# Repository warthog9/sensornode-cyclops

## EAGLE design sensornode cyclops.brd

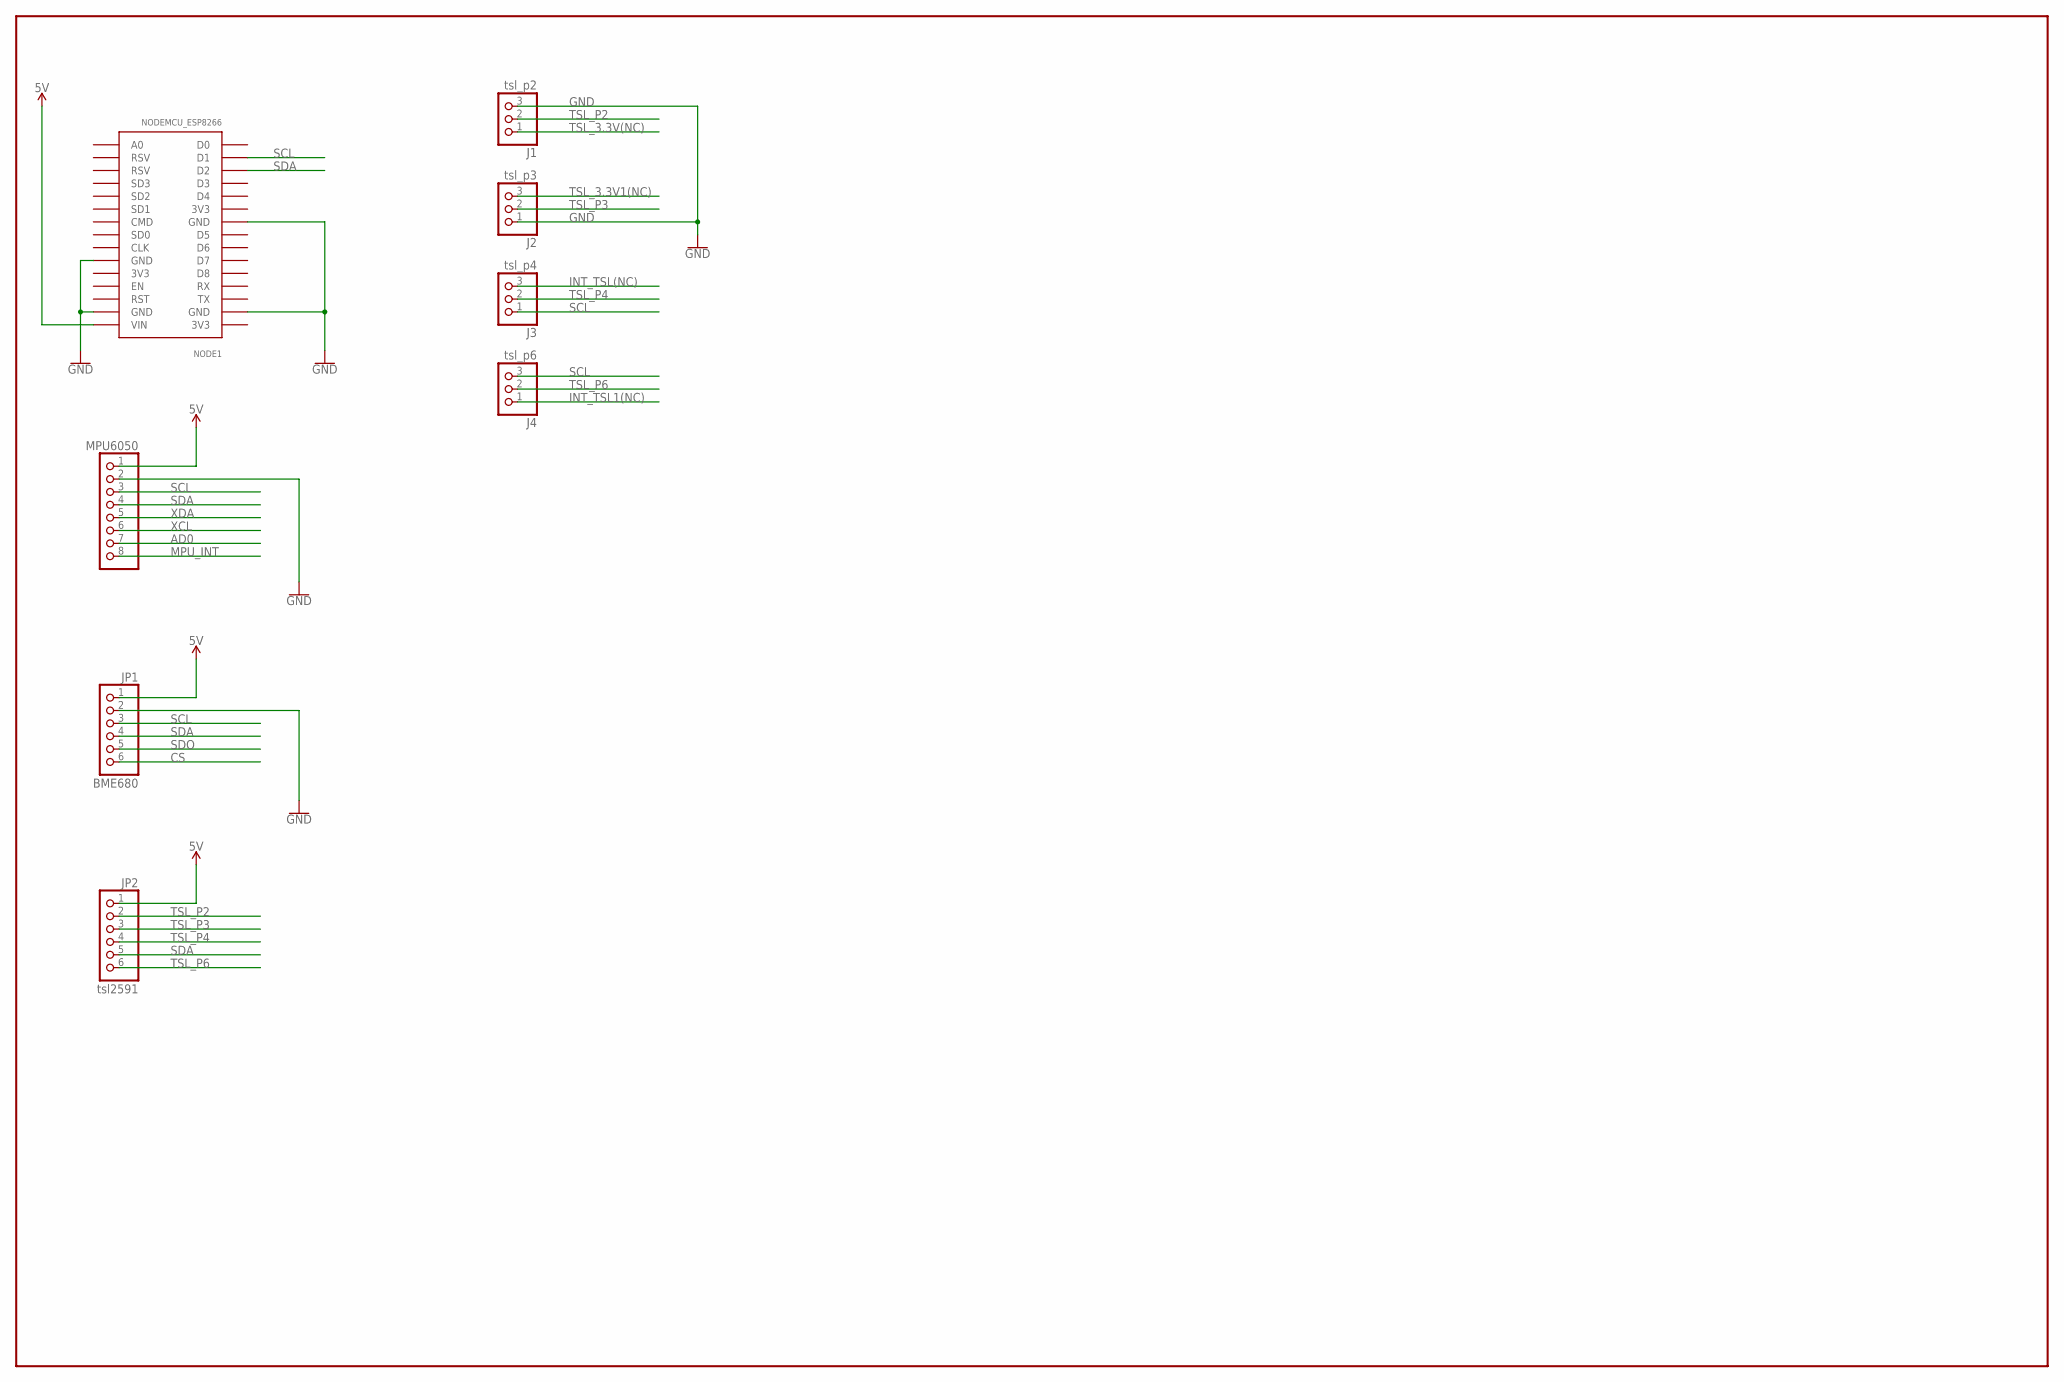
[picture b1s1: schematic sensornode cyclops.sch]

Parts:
J1: tsl_p2; 1X03
J2: tsl_p3; 1X03
J3: tsl_p4; 1X03
J4: tsl_p6; 1X03
JP1: BME680; 1X06
JP2: tsl2591; 1X06
MPU6050: PINHD-1X8; 1X08
NODE1: NODEMCU_ESP8266

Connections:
3V3: NODE1.3V3@1 (3V3), NODE1.3V3@2 (3V3), NODE1.3V3@3 (3V3)
5V: JP1.1, JP2.1, MPU6050.1, NODE1.VIN
AD0: MPU6050.7
CS: JP1.6
GND: J1.3, J2.1, JP1.2, MPU6050.2, NODE1.GND@1 (GND), NODE1.GND@2 (GND), NODE1.GND@3 (GND), NODE1.GND@4 (GND)
INT_TSL1(NC): J4.1
INT_TSL(NC): J3.3
MPU_INT: MPU6050.8
SCL: J3.1, J4.3, JP1.3, MPU6050.3, NODE1.D1
SDA: JP1.4, JP2.5, MPU6050.4, NODE1.D2
SDO: JP1.5
TSL_3.3V1(NC): J2.3
TSL_3.3V(NC): J1.1
TSL_P2: J1.2, JP2.2
TSL_P3: J2.2, JP2.3
TSL_P4: J3.2, JP2.4
TSL_P6: J4.2, JP2.6
XCL: MPU6050.6
XDA: MPU6050.5

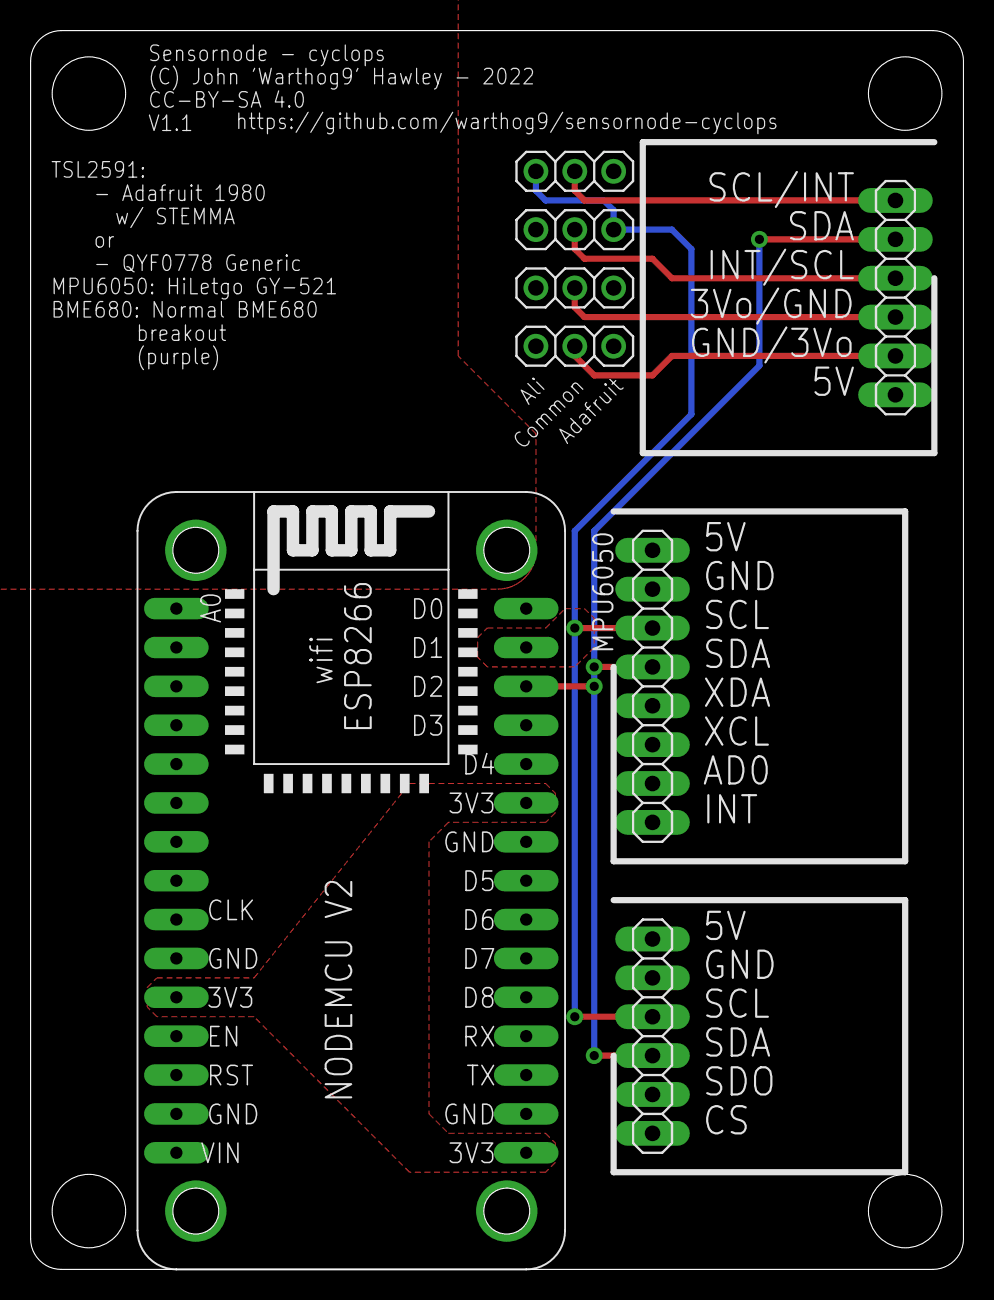
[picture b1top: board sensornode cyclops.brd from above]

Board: 2 copper layers, 61.0 x 81.0 mm, 8 parts (0 on the bottom side), 9 nets.

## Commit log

2022-11-15 Initial commit this is v2

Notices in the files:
sensornode cyclops.brd:
CC-BY-SA 4.0
parts and their libraries:
SparkFun-PowerSymbols: Licensing: Creative Commons ShareAlike 4.0 International - https://creativecommons.org/licenses/by-sa/4.0
